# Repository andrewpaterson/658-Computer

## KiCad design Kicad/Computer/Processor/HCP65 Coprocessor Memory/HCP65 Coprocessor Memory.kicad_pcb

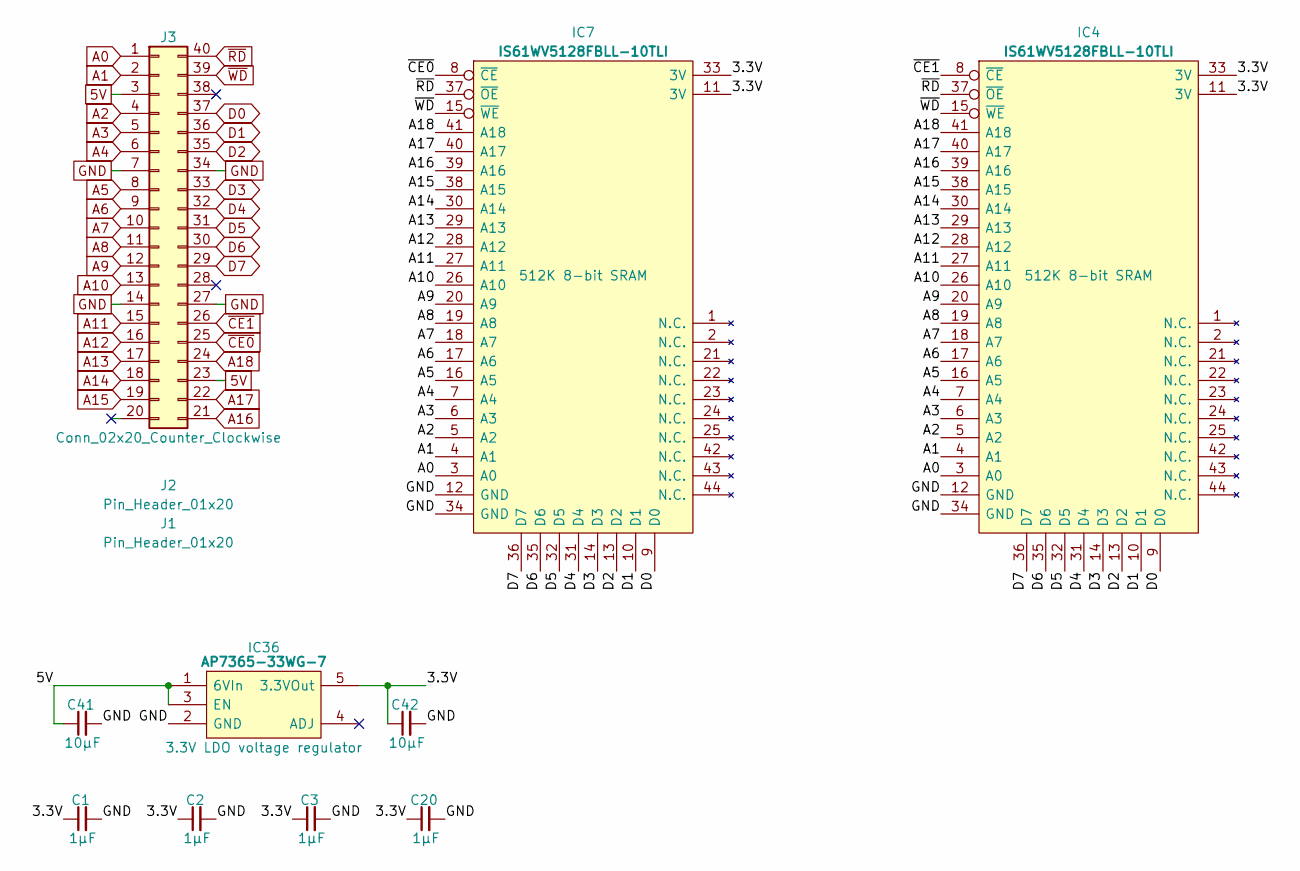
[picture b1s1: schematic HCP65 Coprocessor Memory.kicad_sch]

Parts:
C1, C2, C3, C20: 1μF; C_0805
C41, C42: 10μF; C_0805
IC4, IC7: IS61WV5128FBLL-10TLI; SOP80P1176X120-44N; Manufacturer_Part_Number IS61WV5128FBLL-10TLI
IC36: AP7365-33WG-7; SOT95P285X130-5N; Manufacturer_Part_Number AP7365-33WG-7; Mouser Part Number 621-AP7365-33WG-7
J1, J2: Pin_Header_01x20; PinHeader_1x20_P2.54mm_Vertical
J3: Conn_02x20_Counter_Clockwise; DIP-40_Board_W22.86mm

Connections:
5V: C41.1, IC36.1 (6VIn), IC36.3 (EN), J3.3, J3.23
/3.3V: C1.1, C2.1, C3.1, C20.1, C42.1, IC4.11 (3V), IC4.33 (3V), IC7.11 (3V), IC7.33 (3V), IC36.5 (3.3VOut)
A0: IC4.3 (A0), IC7.3 (A0), J3.1
A1: IC4.4 (A1), IC7.4 (A1), J3.2
A2: IC4.5 (A2), IC7.5 (A2), J3.4
A3: IC4.6 (A3), IC7.6 (A3), J3.5
A4: IC4.7 (A4), IC7.7 (A4), J3.6
A5: IC4.16 (A5), IC7.16 (A5), J3.8
A6: IC4.17 (A6), IC7.17 (A6), J3.9
A7: IC4.18 (A7), IC7.18 (A7), J3.10
A8: IC4.19 (A8), IC7.19 (A8), J3.11
A9: IC4.20 (A9), IC7.20 (A9), J3.12
A10: IC4.26 (A10), IC7.26 (A10), J3.13
A11: IC4.27 (A11), IC7.27 (A11), J3.15
A12: IC4.28 (A12), IC7.28 (A12), J3.16
A13: IC4.29 (A13), IC7.29 (A13), J3.17
A14: IC4.30 (A14), IC7.30 (A14), J3.18
A15: IC4.38 (A15), IC7.38 (A15), J3.19
A16: IC4.39 (A16), IC7.39 (A16), J3.21
A17: IC4.40 (A17), IC7.40 (A17), J3.22
A18: IC4.41 (A18), IC7.41 (A18), J3.24
D0: IC4.9 (D0), IC7.9 (D0), J3.37
D1: IC4.10 (D1), IC7.10 (D1), J3.36
D2: IC4.13 (D2), IC7.13 (D2), J3.35
D3: IC4.14 (D3), IC7.14 (D3), J3.33
D4: IC4.31 (D4), IC7.31 (D4), J3.32
D5: IC4.32 (D5), IC7.32 (D5), J3.31
D6: IC4.35 (D6), IC7.35 (D6), J3.30
D7: IC4.36 (D7), IC7.36 (D7), J3.29
GND: C1.2, C2.2, C3.2, C20.2, C41.2, C42.2, IC4.12 (GND), IC4.34 (GND), IC7.12 (GND), IC7.34 (GND), IC36.2 (GND), J3.7, J3.14, J3.27, J3.34
~CE0: IC7.8 (~CE), J3.25
~CE1: IC4.8 (~CE), J3.26
~RD: IC4.37 (~OE), IC7.37 (~OE), J3.40
~WD: IC4.15 (~WE), IC7.15 (~WE), J3.39

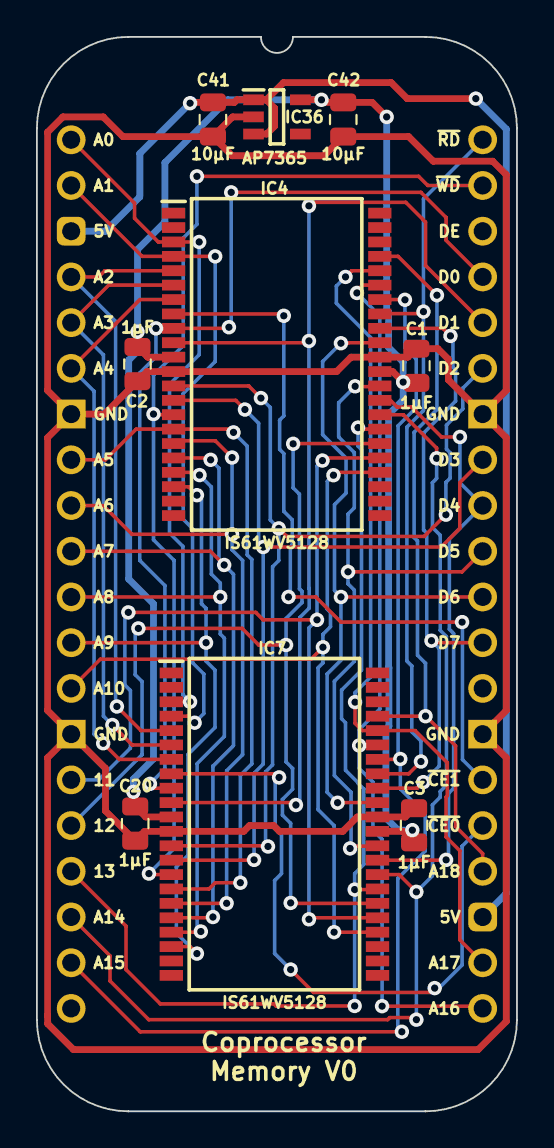
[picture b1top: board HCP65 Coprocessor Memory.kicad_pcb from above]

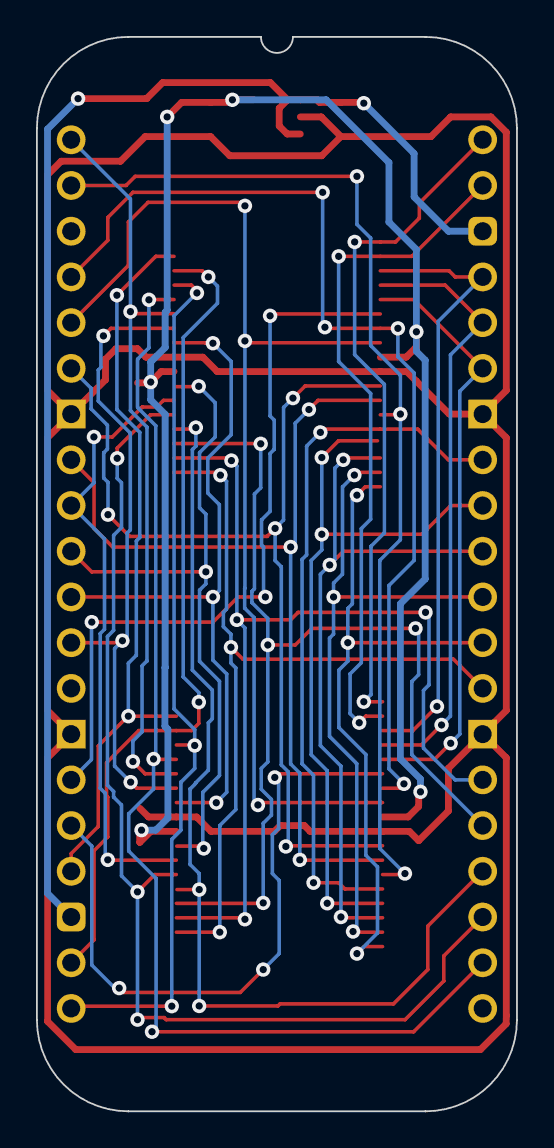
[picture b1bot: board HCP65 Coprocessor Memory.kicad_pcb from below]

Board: 2 copper layers, 26.7 x 59.7 mm, 12 parts (2 on the bottom side), 34 nets.

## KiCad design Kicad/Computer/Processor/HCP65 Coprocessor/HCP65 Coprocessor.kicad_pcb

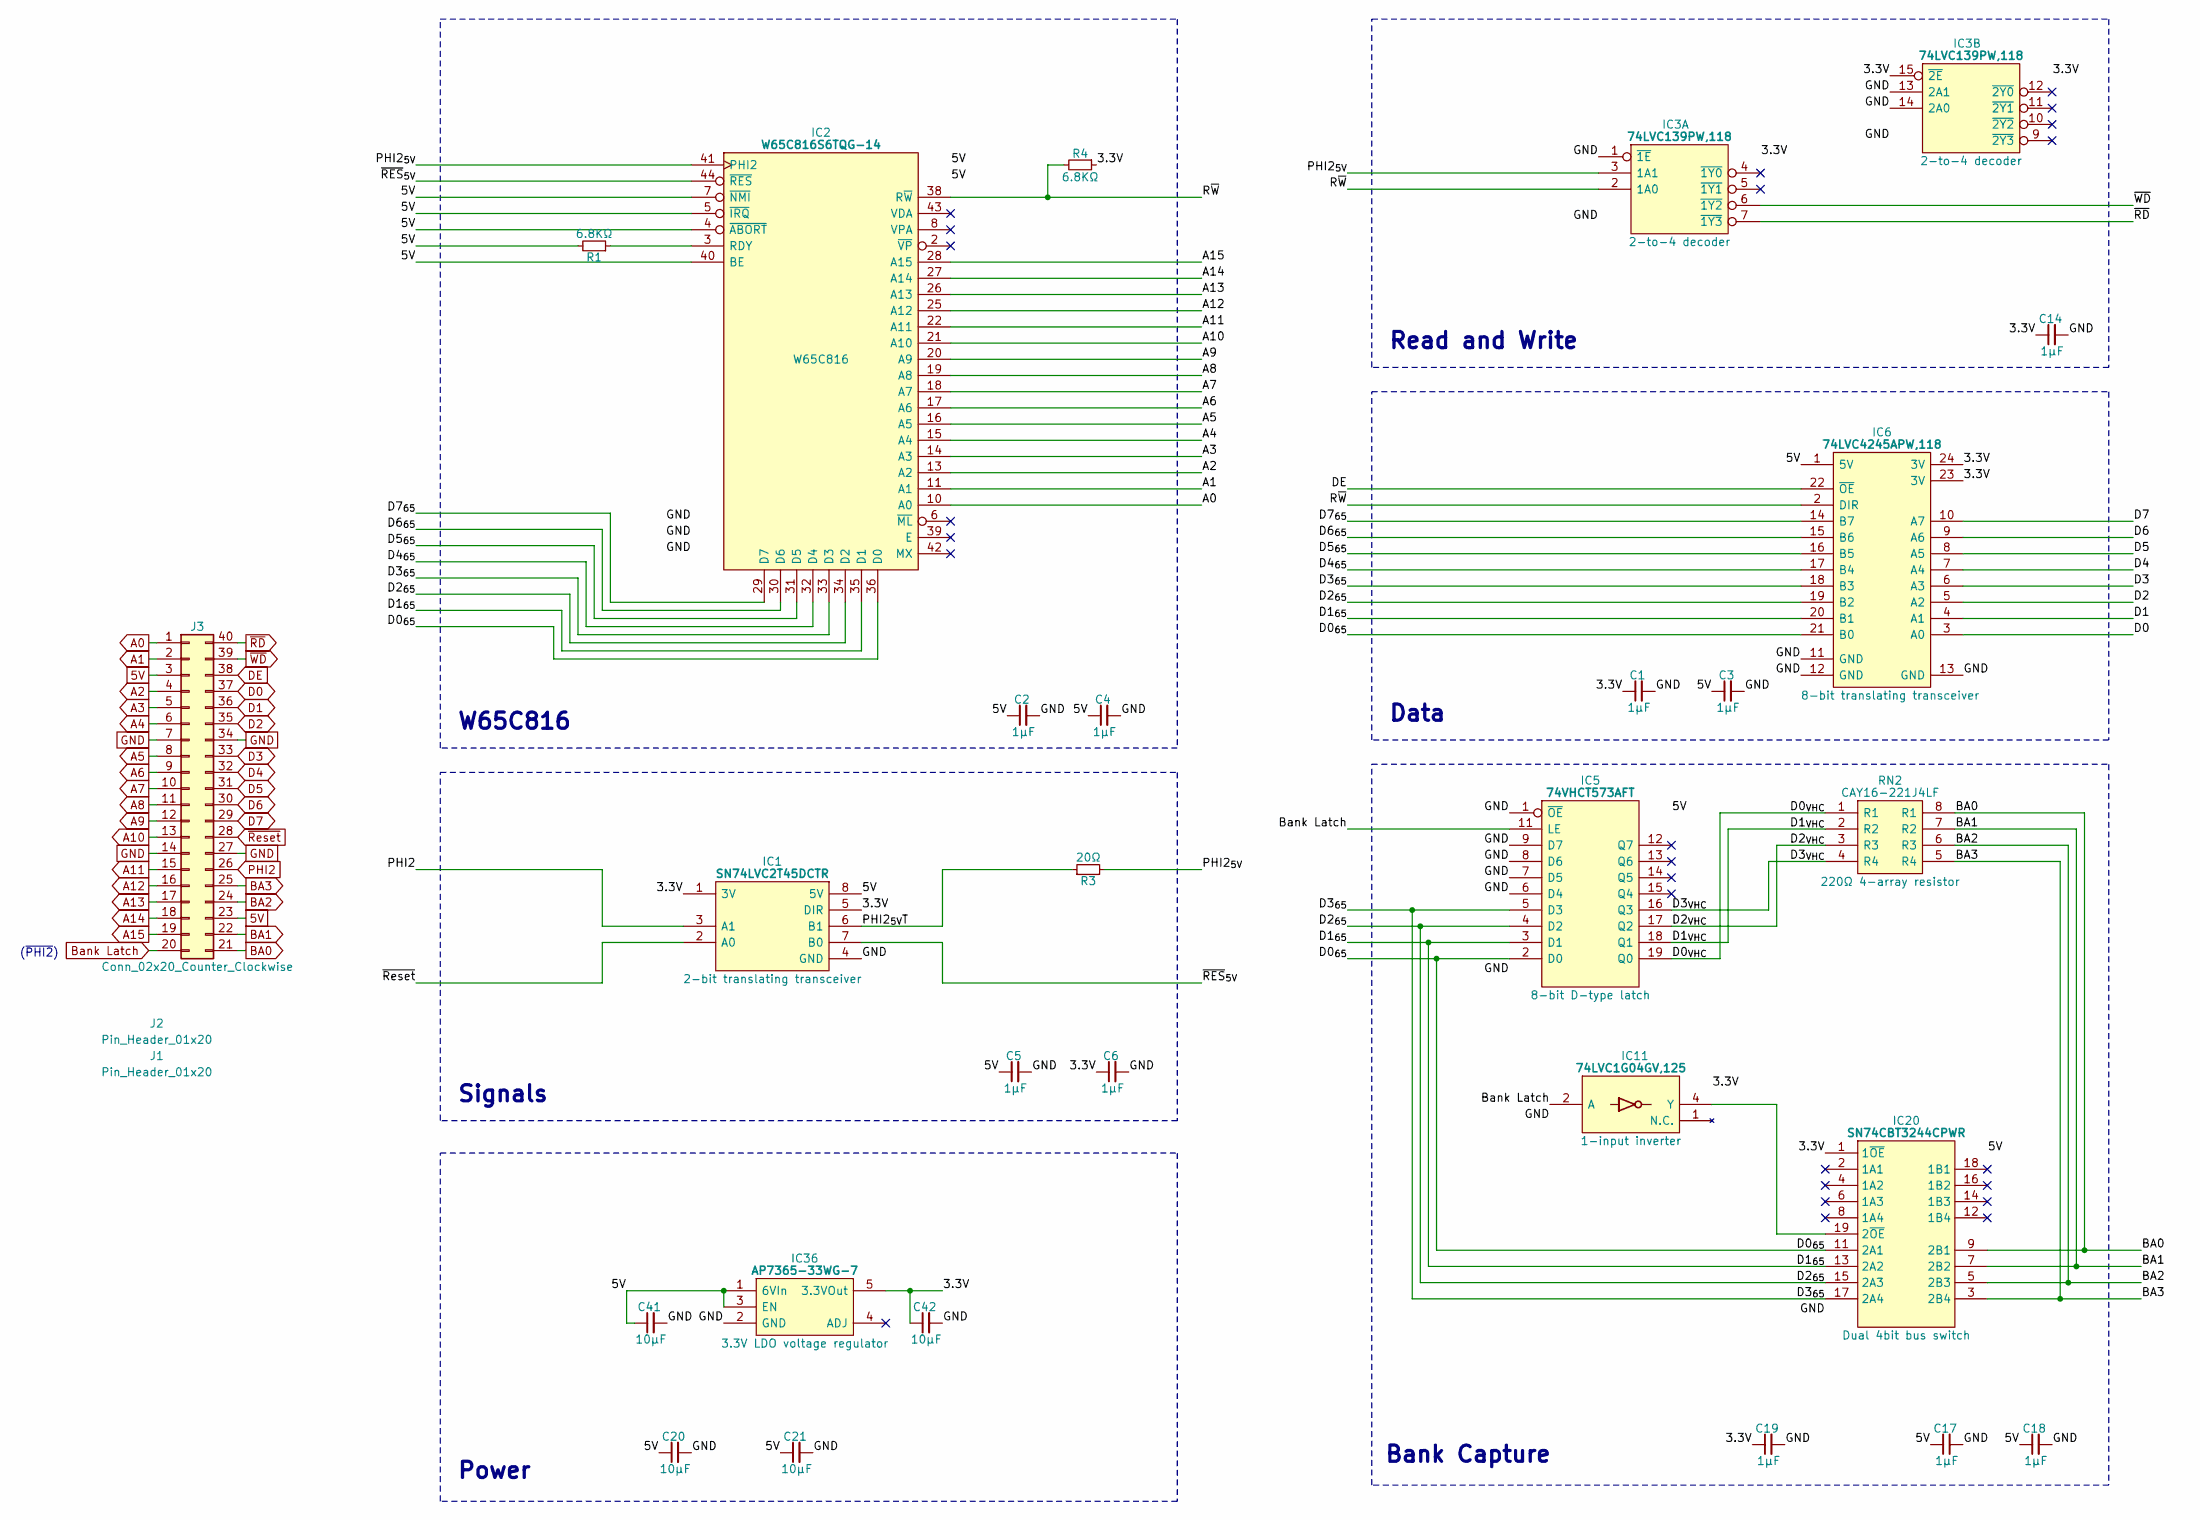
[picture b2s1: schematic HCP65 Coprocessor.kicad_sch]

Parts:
C1, C2, C3, C4, C5, C6, C14, C17, C18, C19: 1μF; C_0805
C20, C21, C41, C42: 10μF; C_0805
IC1: SN74LVC2T45DCTR; SOP65P400X130-8N; Manufacturer_Part_Number SN74LVC2T45DCTR
IC2: W65C816S6TQG-14; W65C816 PLCC 0.8mm 44 Pin; Mouser Part Number 955-W65C816S6TQG-14
IC3: 74LVC139PW,118; SOP65P640X110-16N
IC5: 74VHCT573AFT; SOP65P640X120-20N; Manufacturer_Part_Number 74VHCT573AFT; Mouser Part Number N/A
IC6: 74LVC4245APW,118; SOP65P640X110-24N; Mouser Part Number 771-74LVC4245APW-T
IC11: 74LVC1G04GV,125; SOT95P275X110-5N; Manufacturer_Part_Number 74LVC1G04GV,125; Mouser Part Number 771-74LVC1G04GV
IC20: SN74CBT3244CPWR; SOP65P640X120-20N; Manufacturer_Part_Number SN74CBT3244CPWR; Mouser Part Number 595-SN74CBT3244CPWR
IC36: AP7365-33WG-7; SOT95P285X130-5N; Manufacturer_Part_Number AP7365-33WG-7; Mouser Part Number 621-AP7365-33WG-7
J1, J2: Pin_Header_01x20; PinHeader_1x20_P2.54mm_Vertical
J3: Conn_02x20_Counter_Clockwise; DIP-40_Board_W22.86mm
R1, R4: 6.8KΩ; R_0805
R3: 20Ω; R_0805
RN2: CAY16-221J4LF; CAY16-F4; Manufacturer_Part_Number CAY16-221J4LF; Mouser Part Number 652-CAY16-221J4LF

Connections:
5V: C2.1, C3.1, C4.1, C5.1, C17.1, C18.1, C20.1, C21.1, C41.1, IC1.8 (5V), IC2.4 (~ABORT), IC2.5 (~IRQ), IC2.7 (~NMI), IC2.9 (VCC), IC2.37 (VCC), IC2.40 (BE), IC5.20 (5V), IC6.1 (5V), IC20.20 (5V), IC36.1 (6VIn), IC36.3 (EN), J3.3, J3.23, R1.2
/3.3V: C1.1, C6.1, C14.1, C19.1, C42.1, IC1.1 (3V), IC1.5 (DIR), IC3.15 (~2E), IC3.16 (3V), IC6.23 (3V), IC6.24 (3V), IC11.5 (3V), IC20.1 (1~OE), IC36.5 (3.3VOut), R4.1
/D0_{65}: IC2.36 (D0), IC5.2 (D0), IC6.21 (B0), IC20.11 (2A1)
/D0_{VHC}: IC5.19 (Q0), RN2.1 (R1)
/D1_{65}: IC2.35 (D1), IC5.3 (D1), IC6.20 (B1), IC20.13 (2A2)
/D1_{VHC}: IC5.18 (Q1), RN2.2 (R2)
/D2_{65}: IC2.34 (D2), IC5.4 (D2), IC6.19 (B2), IC20.15 (2A3)
/D2_{VHC}: IC5.17 (Q2), RN2.3 (R3)
/D3_{65}: IC2.33 (D3), IC5.5 (D3), IC6.18 (B3), IC20.17 (2A4)
/D3_{VHC}: IC5.16 (Q3), RN2.4 (R4)
/D4_{65}: IC2.32 (D4), IC6.17 (B4)
/D5_{65}: IC2.31 (D5), IC6.16 (B5)
/D6_{65}: IC2.30 (D6), IC6.15 (B6)
/D7_{65}: IC2.29 (D7), IC6.14 (B7)
/PHI2_{5V}: IC2.41 (PHI2), IC3.3 (1A1), R3.2
/PHI2_{5V}T: IC1.6 (B1), R3.1
/R~W: IC2.38 (R~W), IC3.2 (1A0), IC6.2 (DIR), R4.2
/~RES_{5V}: IC1.7 (B0), IC2.44 (~RES)
A0: IC2.10 (A0), J3.1
A1: IC2.11 (A1), J3.2
A2: IC2.13 (A2), J3.4
A3: IC2.14 (A3), J3.5
A4: IC2.15 (A4), J3.6
A5: IC2.16 (A5), J3.8
A6: IC2.17 (A6), J3.9
A7: IC2.18 (A7), J3.10
A8: IC2.19 (A8), J3.11
A9: IC2.20 (A9), J3.12
A10: IC2.21 (A10), J3.13
A11: IC2.22 (A11), J3.15
A12: IC2.25 (A12), J3.16
A13: IC2.26 (A13), J3.17
A14: IC2.27 (A14), J3.18
A15: IC2.28 (A15), J3.19
BA0: IC20.9 (2B1), J3.21, RN2.8 (R1)
BA1: IC20.7 (2B2), J3.22, RN2.7 (R2)
BA2: IC20.5 (2B3), J3.24, RN2.6 (R3)
BA3: IC20.3 (2B4), J3.25, RN2.5 (R4)
Bank Latch: IC5.11 (LE), IC11.2 (A), J3.20
D0: IC6.3 (A0), J3.37
D1: IC6.4 (A1), J3.36
D2: IC6.5 (A2), J3.35
D3: IC6.6 (A3), J3.33
D4: IC6.7 (A4), J3.32
D5: IC6.8 (A5), J3.31
D6: IC6.9 (A6), J3.30
D7: IC6.10 (A7), J3.29
DE: IC6.22 (~OE), J3.38
GND: C1.2, C2.2, C3.2, C4.2, C5.2, C6.2, C14.2, C17.2, C18.2, C19.2, C20.2, C21.2, C41.2, C42.2, IC1.4 (GND), IC2.1 (GND), IC2.23 (GND), IC2.24 (GND), IC3.1 (~1E), IC3.8 (GND), IC3.13 (2A1), IC3.14 (2A0), IC5.1 (~OE), IC5.6 (D4), IC5.7 (D5), IC5.8 (D6), IC5.9 (D7), IC5.10 (GND), IC6.11 (GND), IC6.12 (GND), IC6.13 (GND), IC11.3 (GND), IC20.10 (GND), IC36.2 (GND), J3.7, J3.14, J3.27, J3.34
unnamed: IC2.3 (RDY), R1.1
unnamed: IC11.4 (Y), IC20.19 (2~OE)
PHI2: IC1.3 (A1), J3.26
~RD: IC3.7 (~1Y3), J3.40
~Reset: IC1.2 (A0), J3.28
~WD: IC3.6 (~1Y2), J3.39

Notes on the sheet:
(~{PHI2})
Power
Bank Capture
Signals
Read and Write
Data
W65C816

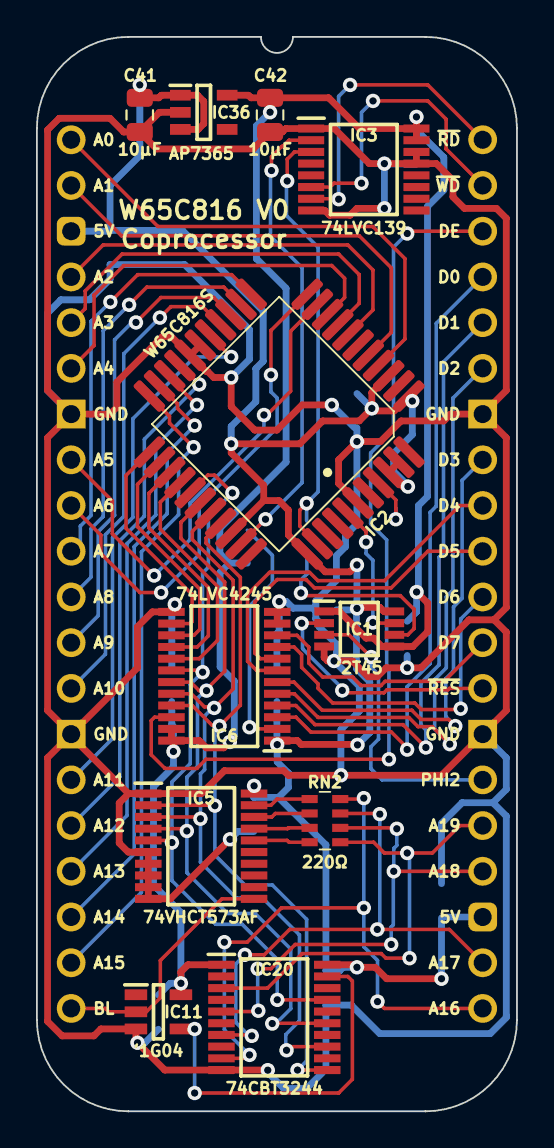
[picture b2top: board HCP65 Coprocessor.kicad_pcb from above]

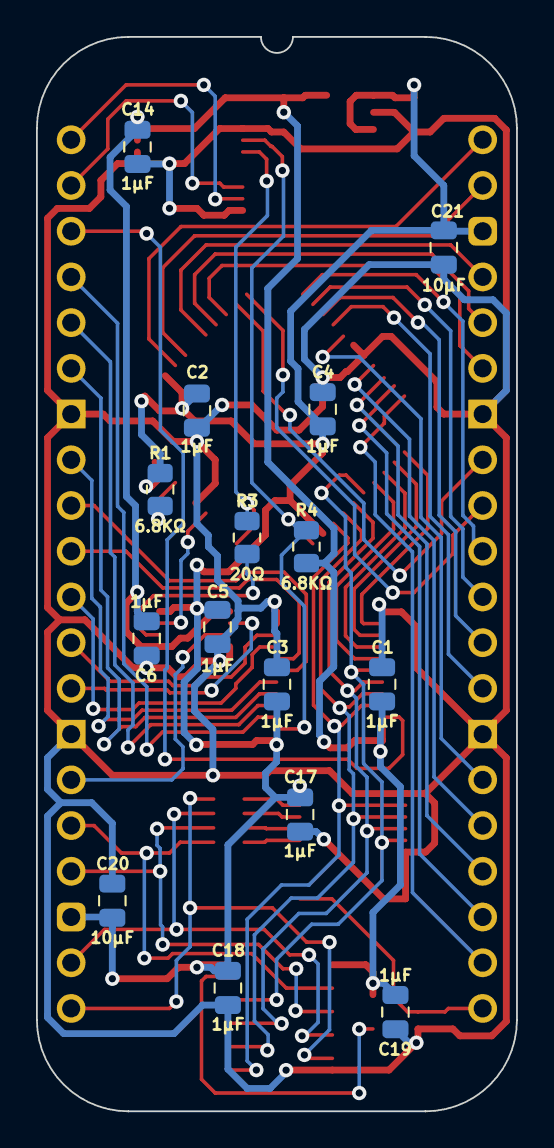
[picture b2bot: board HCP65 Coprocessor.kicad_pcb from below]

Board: 2 copper layers, 26.7 x 59.7 mm, 29 parts (17 on the bottom side), 55 nets.

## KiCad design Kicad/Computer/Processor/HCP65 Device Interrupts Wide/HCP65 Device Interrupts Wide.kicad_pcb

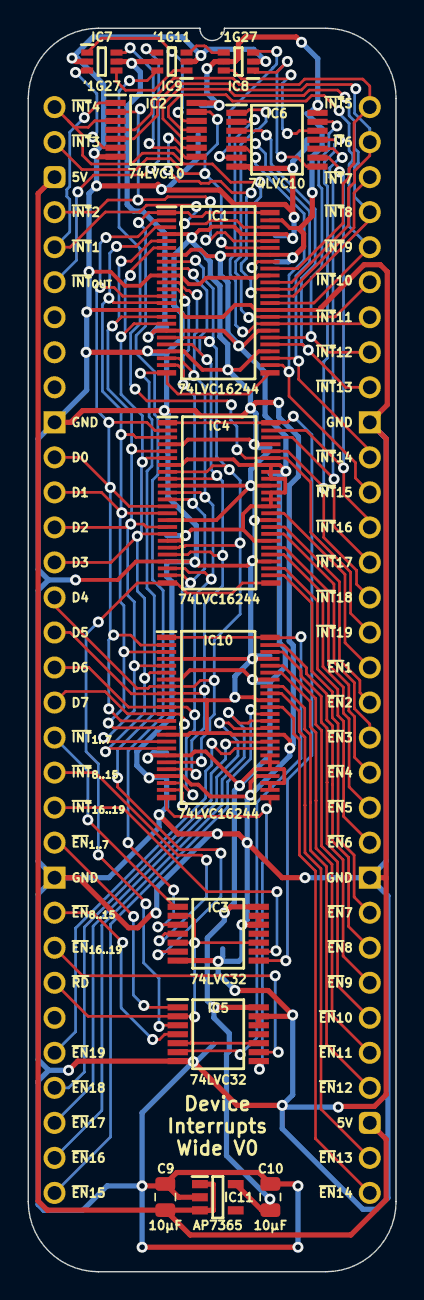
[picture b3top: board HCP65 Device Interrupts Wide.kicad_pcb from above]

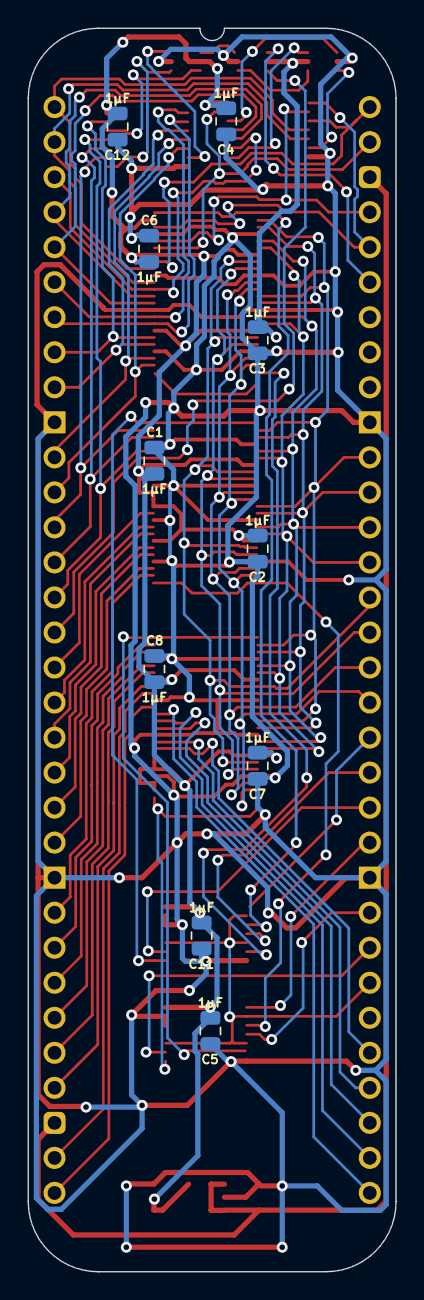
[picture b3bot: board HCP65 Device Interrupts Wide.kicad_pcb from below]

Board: 2 copper layers, 26.7 x 90.2 mm, 26 parts (12 on the bottom side), 71 nets.

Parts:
C1, C2, C3, C4, C5, C6, C7, C8, C11, C12: 1μF; C_0805
C9, C10: 10μF; C_0805
IC1, IC4, IC10: 74LVC16244ADGG,112; 74LVC16244ADGG112
IC2, IC6: SN74LVC10APWR; SOP65P640X120-14N
IC3, IC5: 74LVC32APW,118; SOP65P640X110-14N
IC7, IC8: 74LVC1G27GW,125; SOP65P210X110-6N
IC9: 74LVC1G11GW-Q100H; SOP65P210X110-6N
IC11: AP7365-33WG-7; SOT95P285X130-5N
J1, J3: Pin_Header_01x32; PinHeader_1x32_P2.54mm_Vertical
J2: Conn_02x32_Counter_Clockwise; DIP-64_Board_W22.86mm

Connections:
5V: C9.1, IC11.1 (6VIn), IC11.3 (EN), J2.3, J2.35
/3.3V: C1.1, C2.1, C3.1, C4.1, C5.1, C6.1, C7.1, C8.1, C10.1, C11.1, C12.1, IC1.7 (3V), IC1.18 (3V), IC1.31 (3V), IC1.42 (3V), IC1.47 (1A0), IC2.14 (3V), IC3.14 (3V), IC4.7 (3V), IC4.18 (3V), IC4.31 (3V), IC4.36 (3A0), IC4.37 (2A3), IC4.38 (2A2), IC4.40 (2A1), IC4.41 (2A0), IC4.42 (3V), IC5.14 (3V), IC6.14 (3V), IC7.5 (3V), IC8.5 (3V), IC9.5 (3V), IC10.7 (3V), IC10.18 (3V), IC10.26 (4A3), IC10.27 (4A2), IC10.29 (4A1), IC10.30 (4A0), IC10.31 (3V), IC10.42 (3V), IC11.5 (3.3VOut)
/~Read Device Enable_{ 1..7}: IC4.24 (4~OE), IC4.25 (3~OE), IC5.3 (1Y)
/~Read Device Enable_{ 8..15}: IC5.6 (2Y), IC10.1 (1~OE), IC10.48 (2~OE)
/~Read Device Enable_{ 16..19}: IC5.8 (3Y), IC10.24 (4~OE), IC10.25 (3~OE)
/~Read Device Interrupt_{ 1..7}: IC1.1 (1~OE), IC1.48 (2~OE), IC3.3 (1Y)
/~Read Device Interrupt_{ 8..15}: IC1.24 (4~OE), IC1.25 (3~OE), IC3.6 (2Y)
/~Read Device Interrupt_{ 16..19}: IC3.8 (3Y), IC4.1 (1~OE), IC4.48 (2~OE)
D0: IC1.2 (1Y0), IC1.13 (3Y0), IC4.2 (1Y0), IC4.13 (3Y0), IC10.2 (1Y0), IC10.13 (3Y0), J2.11
D1: IC1.3 (1Y1), IC1.14 (3Y1), IC4.3 (1Y1), IC4.14 (3Y1), IC10.3 (1Y1), IC10.14 (3Y1), J2.12
D2: IC1.5 (1Y2), IC1.16 (3Y2), IC4.5 (1Y2), IC4.16 (3Y2), IC10.5 (1Y2), IC10.16 (3Y2), J2.13
D3: IC1.6 (1Y3), IC1.17 (3Y3), IC4.6 (1Y3), IC4.17 (3Y3), IC10.6 (1Y3), IC10.17 (3Y3), J2.14
D4: IC1.8 (2Y0), IC1.19 (4Y0), IC4.8 (2Y0), IC4.19 (4Y0), IC10.8 (2Y0), IC10.19 (4Y0), J2.15
D5: IC1.9 (2Y1), IC1.20 (4Y1), IC4.9 (2Y1), IC4.20 (4Y1), IC10.9 (2Y1), IC10.20 (4Y1), J2.16
D6: IC1.11 (2Y2), IC1.22 (4Y2), IC4.11 (2Y2), IC4.22 (4Y2), IC10.11 (2Y2), IC10.22 (4Y2), J2.17
D7: IC1.12 (2Y3), IC1.23 (4Y3), IC4.12 (2Y3), IC4.23 (4Y3), IC10.12 (2Y3), IC10.23 (4Y3), J2.18
GND: C1.2, C2.2, C3.2, C4.2, C5.2, C6.2, C7.2, C8.2, C9.2, C10.2, C11.2, C12.2, IC1.4 (GND), IC1.10 (GND), IC1.15 (GND), IC1.21 (GND), IC1.28 (GND), IC1.34 (GND), IC1.39 (GND), IC1.45 (GND), IC2.7 (GND), IC3.7 (GND), IC3.12 (4A), IC3.13 (4B), IC4.4 (GND), IC4.10 (GND), IC4.15 (GND), IC4.21 (GND), IC4.28 (GND), IC4.34 (GND), IC4.39 (GND), IC4.45 (GND), IC5.7 (GND), IC5.12 (4A), IC5.13 (4B), IC6.7 (GND), IC7.2 (GND), IC8.2 (GND), IC9.2 (GND), IC10.4 (GND), IC10.10 (GND), IC10.15 (GND), IC10.21 (GND), IC10.28 (GND), IC10.34 (GND), IC10.39 (GND), IC10.45 (GND), IC11.2 (GND), J2.10, J2.23, J2.42, J2.55
unnamed: IC2.12 (1Y), IC7.1 (A)
unnamed: IC2.6 (2Y), IC7.3 (B)
unnamed: IC2.8 (3Y), IC7.6 (C)
unnamed: IC6.12 (1Y), IC8.6 (C)
unnamed: IC6.6 (2Y), IC8.3 (B)
unnamed: IC6.8 (3Y), IC8.1 (A)
unnamed: IC7.4 (Y), IC9.1 (A)
unnamed: IC8.4 (Y), IC9.3 (B)
~Device Enable_{ 1..7}: IC5.1 (1A), J2.22
~Device Enable_{ 8..15}: IC5.4 (2A), J2.24
~Device Enable_{ 16..19}: IC5.9 (3A), J2.25
~Device Interrupt_{ 1..7}: IC3.1 (1A), J2.19
~Device Interrupt_{ 8..15}: IC3.4 (2A), J2.20
~Device Interrupt_{ 16..19}: IC3.9 (3A), J2.21
~Enable_{Device}1: IC4.35 (3A1), J2.48
~Enable_{Device}2: IC4.33 (3A2), J2.47
~Enable_{Device}3: IC4.32 (3A3), J2.46
~Enable_{Device}4: IC4.30 (4A0), J2.45
~Enable_{Device}5: IC4.29 (4A1), J2.44
~Enable_{Device}6: IC4.27 (4A2), J2.43
~Enable_{Device}7: IC4.26 (4A3), J2.41
~Enable_{Device}8: IC10.47 (1A0), J2.40
~Enable_{Device}9: IC10.46 (1A1), J2.39
~Enable_{Device}10: IC10.44 (1A2), J2.38
~Enable_{Device}11: IC10.43 (1A3), J2.37
~Enable_{Device}12: IC10.41 (2A0), J2.36
~Enable_{Device}13: IC10.40 (2A1), J2.34
~Enable_{Device}14: IC10.38 (2A2), J2.33
~Enable_{Device}15: IC10.37 (2A3), J2.32
~Enable_{Device}16: IC10.36 (3A0), J2.31
~Enable_{Device}17: IC10.35 (3A1), J2.30
~Enable_{Device}18: IC10.33 (3A2), J2.29
~Enable_{Device}19: IC10.32 (3A3), J2.28
~INT: IC9.4 (Y), J2.6
~Interrupt_{Device}1: IC1.46 (1A1), IC2.1 (1A), J2.5
~Interrupt_{Device}2: IC1.44 (1A2), IC2.2 (1B), J2.4
~Interrupt_{Device}3: IC1.43 (1A3), IC2.13 (1C), J2.2
~Interrupt_{Device}4: IC1.41 (2A0), IC2.3 (2A), J2.1
~Interrupt_{Device}5: IC1.40 (2A1), IC2.4 (2B), J2.64
~Interrupt_{Device}6: IC1.38 (2A2), IC2.5 (2C), J2.63
~Interrupt_{Device}7: IC1.37 (2A3), IC2.9 (3A), J2.62
~Interrupt_{Device}8: IC1.36 (3A0), IC2.10 (3B), J2.61
~Interrupt_{Device}9: IC1.35 (3A1), IC2.11 (3C), J2.60
~Interrupt_{Device}10: IC1.33 (3A2), IC6.1 (1A), J2.59
~Interrupt_{Device}11: IC1.32 (3A3), IC6.2 (1B), J2.58
~Interrupt_{Device}12: IC1.30 (4A0), IC6.13 (1C), J2.57
~Interrupt_{Device}13: IC1.29 (4A1), IC6.3 (2A), J2.56
~Interrupt_{Device}14: IC1.27 (4A2), IC6.4 (2B), J2.54
~Interrupt_{Device}15: IC1.26 (4A3), IC6.5 (2C), J2.53
~Interrupt_{Device}16: IC4.47 (1A0), IC6.9 (3A), J2.52
~Interrupt_{Device}17: IC4.46 (1A1), IC6.10 (3B), J2.51
~Interrupt_{Device}18: IC4.44 (1A2), IC6.11 (3C), J2.50
~Interrupt_{Device}19: IC4.43 (1A3), IC9.6 (C), J2.49
~RD: IC3.2 (1B), IC3.5 (2B), IC3.10 (3B), IC5.2 (1B), IC5.5 (2B), IC5.10 (3B), J2.26

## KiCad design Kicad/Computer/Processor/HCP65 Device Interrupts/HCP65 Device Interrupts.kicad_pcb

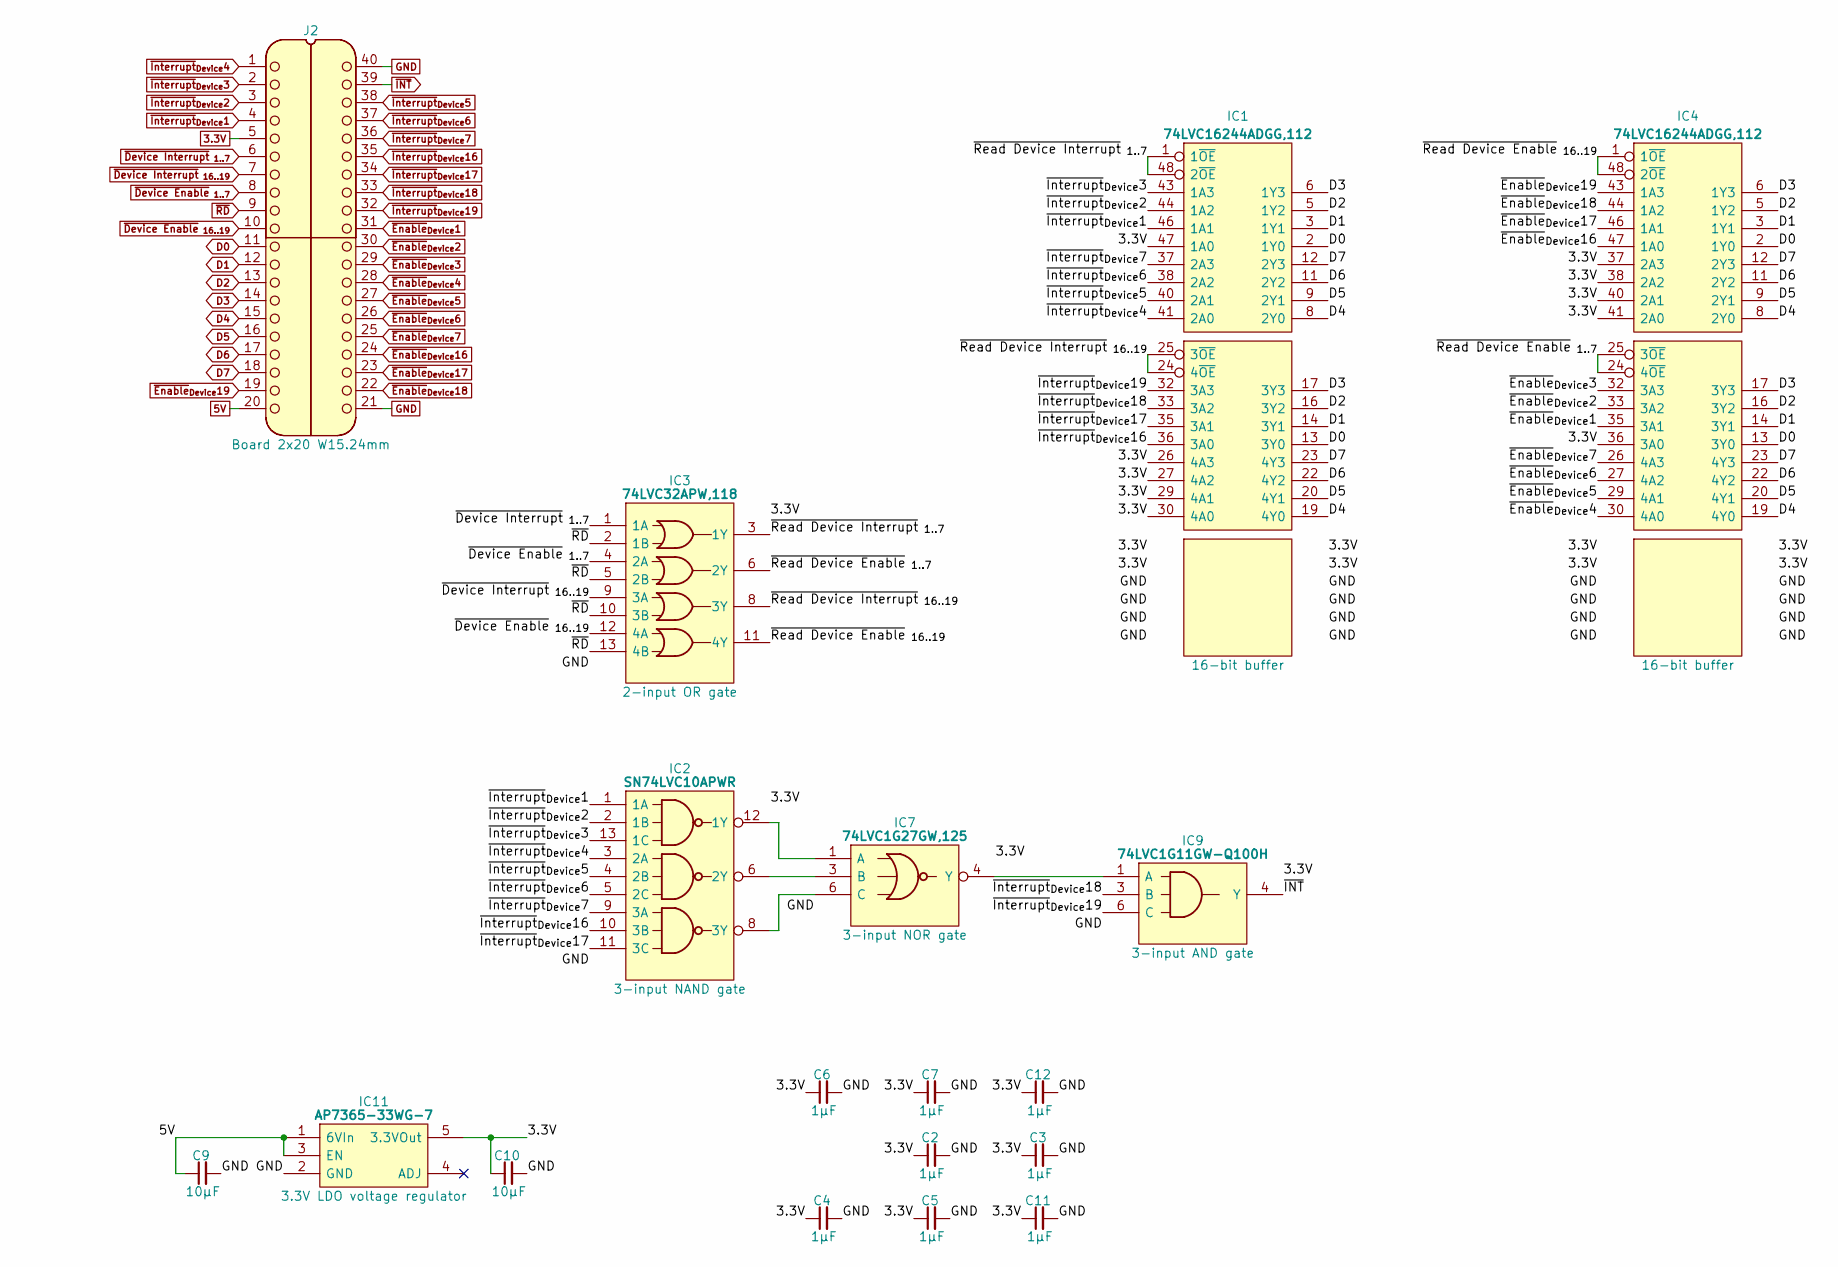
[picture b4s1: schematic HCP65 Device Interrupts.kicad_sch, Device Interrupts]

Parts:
C2, C3, C4, C5, C6, C7, C11, C12: 1μF; C_0805
C9, C10: 10μF; C_0805
IC1, IC4: 74LVC16244ADGG,112; 74LVC16244ADGG112; Manufacturer_Part_Number 74LVC16244ADGG,112; Mouser Part Number 771-74LVC16244DG
IC2: SN74LVC10APWR; SOP65P640X120-14N; Manufacturer_Part_Number SN74LVC10APWR; Mouser Part Number 595-SN74LVC10APWR
IC3: 74LVC32APW,118; SOP65P640X110-14N; Manufacturer_Part_Number 74LVC32APW,118; Mouser Part Number 771-74LVC32APW-T
IC7: 74LVC1G27GW,125; SOP65P210X110-6N; Mouser Part Number 771-74LVC1G27GW125
IC9: 74LVC1G11GW-Q100H; SOP65P210X110-6N; Manufacturer_Part_Number 74LVC1G11GW-Q100H; Mouser Part Number 771-74LVC1G11GWQ100H
IC11: AP7365-33WG-7; SOT95P285X130-5N; Manufacturer_Part_Number AP7365-33WG-7; Mouser Part Number 621-AP7365-33WG-7
J2: Board 2x20 W15.24mm; DIP-40_Board_W15.24mm

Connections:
3.3V: C2.1, C3.1, C4.1, C5.1, C6.1, C7.1, C10.1, C11.1, C12.1, IC1.7 (3V), IC1.18 (3V), IC1.26 (4A3), IC1.27 (4A2), IC1.29 (4A1), IC1.30 (4A0), IC1.31 (3V), IC1.42 (3V), IC1.47 (1A0), IC2.14 (3V), IC3.14 (3V), IC4.7 (3V), IC4.18 (3V), IC4.31 (3V), IC4.36 (3A0), IC4.37 (2A3), IC4.38 (2A2), IC4.40 (2A1), IC4.41 (2A0), IC4.42 (3V), IC7.5 (3V), IC9.5 (3V), IC11.5 (3.3VOut), J2.5
5V: C9.1, IC11.1 (6VIn), IC11.3 (EN), J2.20
/~Read Device Enable_{ 1..7}: IC3.6 (2Y), IC4.24 (4~OE), IC4.25 (3~OE)
/~Read Device Enable_{ 16..19}: IC3.11 (4Y), IC4.1 (1~OE), IC4.48 (2~OE)
/~Read Device Interrupt_{ 1..7}: IC1.1 (1~OE), IC1.48 (2~OE), IC3.3 (1Y)
/~Read Device Interrupt_{ 16..19}: IC1.24 (4~OE), IC1.25 (3~OE), IC3.8 (3Y)
D0: IC1.2 (1Y0), IC1.13 (3Y0), IC4.2 (1Y0), IC4.13 (3Y0), J2.11
D1: IC1.3 (1Y1), IC1.14 (3Y1), IC4.3 (1Y1), IC4.14 (3Y1), J2.12
D2: IC1.5 (1Y2), IC1.16 (3Y2), IC4.5 (1Y2), IC4.16 (3Y2), J2.13
D3: IC1.6 (1Y3), IC1.17 (3Y3), IC4.6 (1Y3), IC4.17 (3Y3), J2.14
D4: IC1.8 (2Y0), IC1.19 (4Y0), IC4.8 (2Y0), IC4.19 (4Y0), J2.15
D5: IC1.9 (2Y1), IC1.20 (4Y1), IC4.9 (2Y1), IC4.20 (4Y1), J2.16
D6: IC1.11 (2Y2), IC1.22 (4Y2), IC4.11 (2Y2), IC4.22 (4Y2), J2.17
D7: IC1.12 (2Y3), IC1.23 (4Y3), IC4.12 (2Y3), IC4.23 (4Y3), J2.18
GND: C2.2, C3.2, C4.2, C5.2, C6.2, C7.2, C9.2, C10.2, C11.2, C12.2, IC1.4 (GND), IC1.10 (GND), IC1.15 (GND), IC1.21 (GND), IC1.28 (GND), IC1.34 (GND), IC1.39 (GND), IC1.45 (GND), IC2.7 (GND), IC3.7 (GND), IC4.4 (GND), IC4.10 (GND), IC4.15 (GND), IC4.21 (GND), IC4.28 (GND), IC4.34 (GND), IC4.39 (GND), IC4.45 (GND), IC7.2 (GND), IC9.2 (GND), IC11.2 (GND), J2.21, J2.40
unnamed: IC2.12 (1Y), IC7.1 (A)
unnamed: IC2.6 (2Y), IC7.3 (B)
unnamed: IC2.8 (3Y), IC7.6 (C)
unnamed: IC7.4 (Y), IC9.1 (A)
~Device Enable_{ 1..7}: IC3.4 (2A), J2.8
~Device Enable_{ 16..19}: IC3.12 (4A), J2.10
~Device Interrupt_{ 1..7}: IC3.1 (1A), J2.6
~Device Interrupt_{ 16..19}: IC3.9 (3A), J2.7
~Enable_{Device}1: IC4.35 (3A1), J2.31
~Enable_{Device}2: IC4.33 (3A2), J2.30
~Enable_{Device}3: IC4.32 (3A3), J2.29
~Enable_{Device}4: IC4.30 (4A0), J2.28
~Enable_{Device}5: IC4.29 (4A1), J2.27
~Enable_{Device}6: IC4.27 (4A2), J2.26
~Enable_{Device}7: IC4.26 (4A3), J2.25
~Enable_{Device}16: IC4.47 (1A0), J2.24
~Enable_{Device}17: IC4.46 (1A1), J2.23
~Enable_{Device}18: IC4.44 (1A2), J2.22
~Enable_{Device}19: IC4.43 (1A3), J2.19
~INT: IC9.4 (Y), J2.39
~Interrupt_{Device}1: IC1.46 (1A1), IC2.1 (1A), J2.4
~Interrupt_{Device}2: IC1.44 (1A2), IC2.2 (1B), J2.3
~Interrupt_{Device}3: IC1.43 (1A3), IC2.13 (1C), J2.2
~Interrupt_{Device}4: IC1.41 (2A0), IC2.3 (2A), J2.1
~Interrupt_{Device}5: IC1.40 (2A1), IC2.4 (2B), J2.38
~Interrupt_{Device}6: IC1.38 (2A2), IC2.5 (2C), J2.37
~Interrupt_{Device}7: IC1.37 (2A3), IC2.9 (3A), J2.36
~Interrupt_{Device}16: IC1.36 (3A0), IC2.10 (3B), J2.35
~Interrupt_{Device}17: IC1.35 (3A1), IC2.11 (3C), J2.34
~Interrupt_{Device}18: IC1.33 (3A2), IC9.3 (B), J2.33
~Interrupt_{Device}19: IC1.32 (3A3), IC9.6 (C), J2.32
~RD: IC3.2 (1B), IC3.5 (2B), IC3.10 (3B), IC3.13 (4B), J2.9

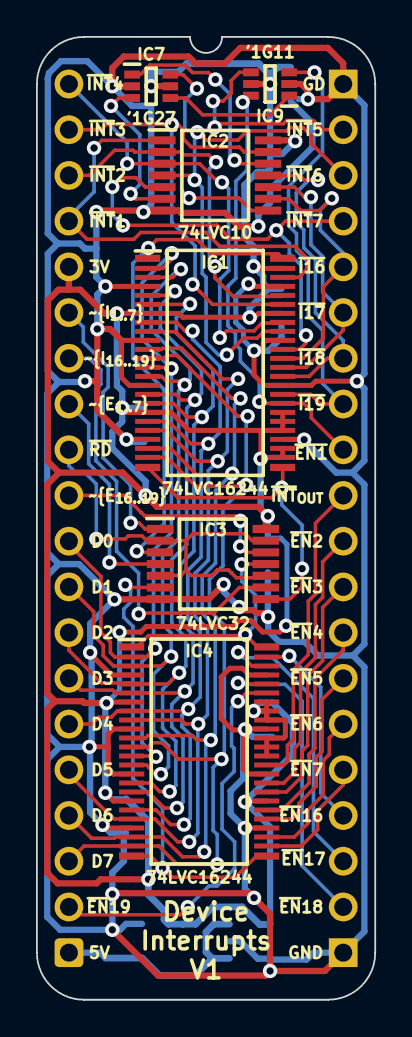
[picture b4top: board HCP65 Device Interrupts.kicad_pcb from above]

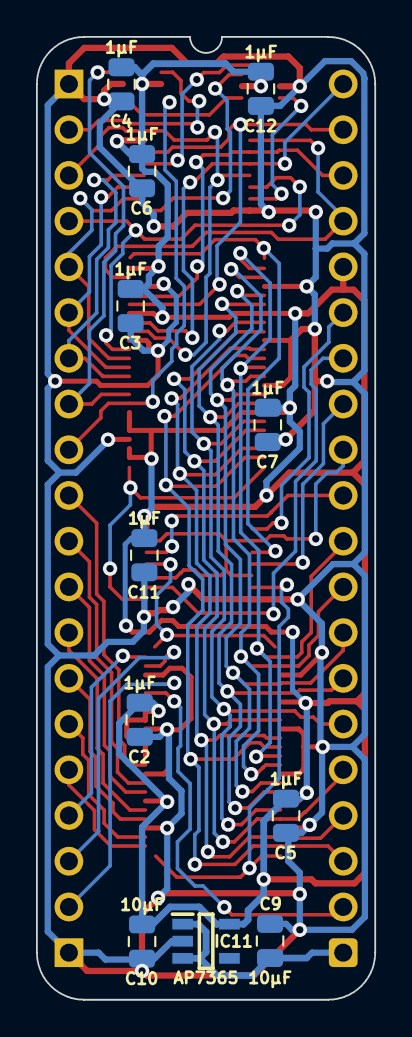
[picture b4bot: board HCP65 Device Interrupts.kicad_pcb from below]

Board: 2 copper layers, 18.8 x 53.5 mm, 18 parts (11 on the bottom side), 47 nets.
